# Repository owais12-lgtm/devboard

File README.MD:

# About

This is a RP2040 based Pi Pico clone 
# features

    Dual-core M0+ processor
    Flexible clock running up to 133 MHz
    264 kB of SRAM
    USB 1.1 controller and PHY with device and host support
    Low-power sleep and dormant modes
    Accurate clock and timer
    Accelerated floating-point libraries
    Temperature sensor
    Eight Programmable I/O (PIO) state machines for custom peripheral support

# PCB

# schematic

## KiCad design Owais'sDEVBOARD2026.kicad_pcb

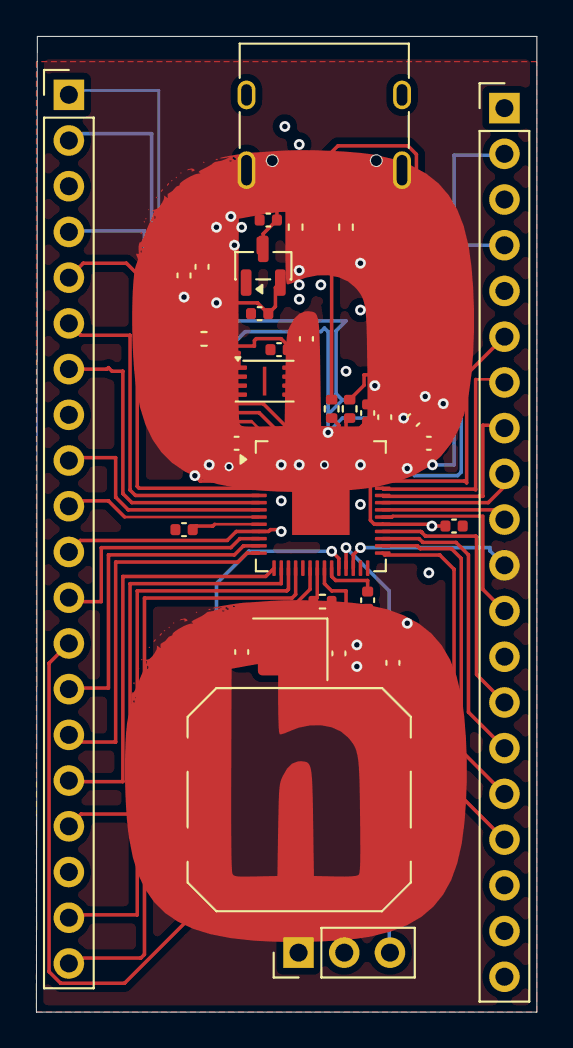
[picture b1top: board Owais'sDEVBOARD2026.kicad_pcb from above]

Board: 2 copper layers, 27.8 x 54.2 mm, 32 parts (0 on the bottom side), 51 nets.

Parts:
C1, C10: 1uF; C_0402_1005Metric
C2, C3, C4, C5, C6, C7, C8, C9, C11, C12, C17: 0.1uF; C_0402_1005Metric
C13, C14: 10uF; C_0402_1005Metric
C15, C16: 15pF; C_0402_1005Metric
J1: USB_C_Receptacle_USB2.0_14P; USB_C_Receptacle_HRO_TYPE-C-31-M-12
J2, J3: Conn_01x20; PinHeader_1x20_P2.54mm_Vertical
J4: Conn_01x03; PinHeader_1x03_P2.54mm_Vertical
R1, R2: 5.1K; R_0402_1005Metric
R3, R4: 27; R_0402_1005Metric
R5: 1K; R_0402_1005Metric
R7: 10K; R_0402_1005Metric
SW1: SW_Push; SW_Push_1P1T_NO_CK_PTS125Sx85SMTR
U1: RP2040; QFN-56-1EP_7x7mm_P0.4mm_EP3.2x3.2mm
U3: W25Q128JVS; Winbond_USON-8-1EP_3x2mm_P0.5mm_EP0.2x1.6mm
U4: MCP1700x-330xxTT; SOT-23
Y1: 12 MHz; Crystal_SMD_3225-4Pin_3.2x2.5mm

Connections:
+1V1: C10.1, C11.1, C12.1, U1.23 (DVDD), U1.45 (VREG_VOUT), U1.50 (DVDD)
+3V3: C1.1, C2.1, C3.1, C4.1, C5.1, C6.1, C7.1, C8.1, C9.1, C14.1, C17.1, J3.5, R7.1, U1.1 (IOVDD), U1.10 (IOVDD), U1.22 (IOVDD), U1.33 (IOVDD), U1.42 (IOVDD), U1.43 (ADC_AVDD), U1.44 (VREG_VIN), U1.48 (USB_VDD), U1.49 (IOVDD), U3.8 (VCC), U4.2 (VO)
GPIO0: J2.1, U1.2 (GPIO0)
GPIO1: J2.2, U1.3 (GPIO1)
GPIO2: J2.4, U1.4 (GPIO2)
GPIO3: J2.5, U1.5 (GPIO3)
GPIO4: J2.6, U1.6 (GPIO4)
GPIO5: J2.7, U1.7 (GPIO5)
GPIO6: J2.9, U1.8 (GPIO6)
GPIO7: J2.10, U1.9 (GPIO7)
GPIO8: J2.11, U1.11 (GPIO8)
GPIO9: J2.12, U1.12 (GPIO9)
GPIO10: J2.14, U1.13 (GPIO10)
GPIO11: J2.15, U1.14 (GPIO11)
GPIO12: J2.16, U1.15 (GPIO12)
GPIO13: J2.17, U1.16 (GPIO13)
GPIO14: J2.19, U1.17 (GPIO14)
GPIO15: J2.20, U1.18 (GPIO15)
GPIO16: J3.20, U1.27 (GPIO16)
GPIO17: J3.19, U1.28 (GPIO17)
GPIO18: J3.17, U1.29 (GPIO18)
GPIO19: J3.16, U1.30 (GPIO19)
GPIO20: J3.15, U1.31 (GPIO20)
GPIO21: J3.14, U1.32 (GPIO21)
GPIO22: J3.12, U1.34 (GPIO22)
GPIO23: J3.10, U1.35 (GPIO23)
GPIO24: J3.9, U1.36 (GPIO24)
GPIO25: C1.2, C2.2, C3.2, C5.2, C6.2, C7.2, C8.2, C9.2, C10.2, C11.2, C12.2, C13.2, C14.2, C15.1, C16.1, C17.2, J1.A1 (GND), J1.A12 (GND), J1.B1 (GND), J1.B12 (GND), J1.SH (SHIELD), J2.3, J2.8, J2.13, J2.18, J3.3, J3.8, J3.13, J3.18, J4.2, R1.2, R2.1, SW1.1, U1.37 (GPIO25), U1.57 (GND), U3.4 (GND), U4.1 (GND), Y1.2 (G), Y1.4 (G)
GPIO26: J3.7, U1.38 (GPIO26/ADC0)
GPIO27: J3.6, U1.39 (GPIO27/ADC1)
GPIO28: J3.4, U1.40 (GPIO28/ADC2)
GPIO29: J3.2, U1.41 (GPIO29/ADC3)
unnamed: C16.2, R5.1, Y1.1
unnamed: J1.A5 (CC1), R1.1
unnamed: J1.B5 (CC2), R2.2
unnamed: R3.2, U1.46 (USB_DM)
unnamed: R4.2, U1.47 (USB_DP)
QSPI_SCLK: U1.52 (QSPI_SCLK), U3.6 (CLK)
QSPI_SD0: U1.53 (QSPI_SD0), U3.5 (DI/IO_{0})
QSPI_SD1: U1.55 (QSPI_SD1), U3.2 (DO/IO_{1})
QSPI_SD2: U1.54 (QSPI_SD2), U3.3 (~WP/IO_{2})
QSPI_SD3: U1.51 (QSPI_SD3), U3.7 (~HOLD/~RESET/IO_{3})
QSPI_SS: R7.2, U1.56 (~QSPI_SS), U3.1 (~CS)
RUN: J3.11, U1.26 (RUN)
SWCLK: J4.1, U1.24 (SWCLK)
SWD: J4.3, U1.25 (SWDIO)
USB_D+: J1.A6 (D+), J1.B6 (D+), R3.1
USB_D-: J1.A7 (D-), J1.B7 (D-), R4.1
VBUS: C13.1, J1.A4 (VBUS), J1.A9 (VBUS), J1.B4 (VBUS), J1.B9 (VBUS), J3.1, U4.3 (VI)
XIN: C15.2, U1.20 (XIN), Y1.3
XOUT: R5.2, U1.21 (XOUT)
